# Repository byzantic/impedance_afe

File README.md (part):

# Impedance / C-V / DLTS / Electrochemistry Analog Front End: Rev B

**Status:** the Rev B **schematic** is done; the **PCB** is placed, the critical nets are hand-routed and locked, and the rest is autorouted (Freerouting): DRC 0 unconnected, 0 copper violations, parity 0; silkscreen not yet tidied. Rev A (schematic plus routed board, converted to KiCad 9/10) is kept in [`revA/`](revA/).

Fabrication outputs go in [GitHub Releases](../../releases), not in the repo. The parts list with debug and precision columns is in [`docs/BOM_revB.csv`](docs/BOM_revB.csv).

## Changes from Rev A
| Area | Rev A | Rev B |
|---|---|---|
| Drive input | single VIN BNC | **BIAS/PULSE** (DC) + **AC PROBE** (AC-coupled, ×1/×0.1 jumper) + **on-board 16-bit bias DAC**, summed (U9/U10) |
| C/G null | none | **vector nuller**: RV1 → fixed C (100 pF / 1 nF) and RV2 → fixed R (20 k / 2 k, AC-coupled), driven from the measured RE voltage |
| Calibration | none | T-switched on-board **10 k 0.1 %** and **100 pF 1 %** loads (CE_INT → WE) |
| Cell | always connected | **CELL relay** (K10) disconnects CE |
| High-gain ranges | 10k…100M | **1k**, 10k, 100k, 1M, 10M, 100M |
| V monitor | V_RE/2 only | V_OUT BNC switched by **VMODE**: DC (V_RE/2) or **AC ×10.1** (100 Hz HPF) |
| Control | 8 GPIOs → 74HCT541 | **Pico 2 or ESP32-S3-ETH** (socketed), SPI → 2× 74HC595 → 16 lines → 2× TBD62783A source drivers |
| Digitiser | scope only | adds an on-board **ADS131M04** (4-ch simultaneous, 24-bit) for standalone potentiostat work |
| Parts | SMD | **through-hole** throughout, except DAC/ADC (JLC-placed) and the SOIC half of the op-amp footprints |
| Op-amp footprint | SOIC-8 | **DIP-8 + SOIC-8 combo** (`afe:DIP-8_SOIC-8_Combo`): fit one package |
| Steering diodes | BAV199 (SOT-23) | 2N3904 collector-base junctions (TO-92) |

## Specifications (design values, not measured)
| Parameter | Value |
|---|---|
| Supplies | external ±15 V (screw terminal). On board: +5 V (L7805) and +3.3 V (MCP1700). Estimated ≲300 mA from +15 V (relays + Pico 2; an ESP32-S3-ETH adds roughly 150–350 mA on +5 V), ≲120 mA from −15 V |
| DUT drive | ±10 V, ≥ ±20 mA (op-amp limited), 47 Ω series to CE |
| BIAS/PULSE input | DC-coupled, Z_in ≈ 9.1 kΩ (10 k to virtual ground ∥ 100 k). JP1 = 50 Ω termination |
| AC PROBE input | AC-coupled. ×1: Z_in ≈ 9.1 kΩ, corner 16 Hz. ×0.1: Z_in ≈ 50 kΩ, corner 1.6 Hz. JP2 = 50 Ω termination, JP3 = gain |
| Bias DAC | DAC80502 channel A, 16-bit, +10.05 V … −10.05 V (≈0.31 mV/LSB), 0 V at midscale power-up; K21 connects it |
| High-gain TIA (±5 V out) | 1k: ±5 mA · 10k: ±500 µA · 100k: ±50 µA · 1M: ±5 µA · 10M: ±500 nA · 100M: ±50 nA |
| TIA feedback pole (precision Cf) | 1k: 7.2 MHz · 10k: 1.6 MHz · 100k: 720 kHz · 1M: 160 kHz · 10M/100M: set by strays (tens of kHz or less) |
| 1 MHz C-V ranges | **1k and 10k only**; calibrate gain and phase per range with the cal loads |
| Low-gain TIA | 499 Ω ∥ 68 pF, ±10 mA FS, takes over via the steering diodes when the high-gain TIA saturates (WE then sits ≈0.6 V off ground) |
| Null range | C: 0–100 pF, or 0–1.01 nF (NULL_RNG). G: ±50 µS, or ±505 µS (NULL_RNG) |
| Outputs (BNC, 50 Ω back-terminated) | V_OUT (DC: V_RE/2 · AC: ×10.1 V_RE), I_HI, I_LO |
| Other BNCs | CE, RE (shell = driven guard), GUARD, WE, BIAS/PULSE, AC PROBE, SYNC_IN (to controller pin 22, clamped) |
| ADC / DAC | On the **ADC/DAC HAT** (`adc_hat/`, Pi Zero pHAT outline) plugged onto J16/J17. ADS131M04, ±1.2 V FS behind the main board's /5.02 dividers (±6 V at the outputs). CH0 V_DC, CH1 I_HI, CH2 I_LO, CH3 V_AC. Clock: Pico GP21 GPOUT0 at 8.000 MHz (USB PLL / 6; data rates ×0.977) via J16-7 by default, or the HAT's 8.192 MHz oscillator (HAT JP1). DAC80502 dual DAC also on the HAT (A = bias, B spare on J2 pin 9) |

## Blocks (schematic sheet regions)
| Block | Refs | Notes |
|---|---|---|
| Power | J1, D1–D3, FB1–FB5, U25, U26 | Controller VSYS fed via D3. Controller ground via FB5 (JP5 hard-ties it) |
| Inputs / summer | J2, J3, U9, U10, K21 | VSET = V_bias + V_dac + k·V_ac (two inverting stages). J2/J3 are on the back edge |
| Bias DAC | HAT U2, U11 | level shift on the main board: V = 10.05 V − 4.02·V_DAC. DAC_OUT/DAC_REF arrive on J17. SPI2C strap is on the HAT (R2 = SPI, JP2 = I2C); R6 pulls RSTSEL high (midscale at power-up) |
| Control amp | U1, K7 (DEV), K8 (PSTAT) | DEV: follower. PSTAT: PI (C15 100 p, R15 1 k, R16 10 k): retune for your cells |
| Cell / cal | K9 (RE_LOCAL), K10 (CELL), K11–K14, R18, C16 | cal mid-nodes are grounded by NC relays when off, so the open contacts see 0 V across them (no leakage into WE) |
| RE / guard / monitors | U2, U3, U7, U4, U8, K19/K20 | U7 (RE_MON) feeds the monitors and the nuller, keeping their load off the electrometer U2 |
| Nuller | U12–U14, RV1, RV2, J14, J15, K15–K18 | inject at SUM_HI. C path: −jωC·V. G path: AC-coupled, bipolar. RV1/RV2 are front-panel 10-turn pots on J14/J15 (Molex KK 254: 1 CW, 2 wiper, 3 CCW, 4 cable shield) |
| TIAs | U5 (K1–K6, R41–R46, C41–C46), Q1/Q2, U6 | relays on the output side of the feedback networks |
| ADC link | J16 (Pi 40-pin, male), J17 (1×12 analog, male), R47, R50–R57, C50–C53 | dividers + 10 nF (≈20 kHz) on the main board, one row per channel level with its J17 pin. J17: 1 ADC0P, 3 ADC1P, 5 ADC2P, 7 ADC3P, 10 DAC_OUT, 11 DAC_REF; 2/4/6/8/12 GND (ADCn N tied to GND here); 9 unconnected (HAT DAC_OUTB) |
| Controller | A1 (Pico 2 or ESP32-S3-ETH), U27/U28 (74HC595), U22/U23, R76, J13 | 4.7 k pulls set the power-up state; RLY_OE (R76 pull-up) holds the 595 outputs off until firmware enables them |

## Control map
The 16 relay lines CTL*n* come from two 74HC595s on SPI0 (MOSI → U27 → U28; SCK shared with the HAT, latch = RLY_LATCH). Shift 16 bits, pulse RLY_LATCH, then drive RLY_OE low. RLY_OE is pulled high (R76), so the 595 outputs stay Hi-Z through power-up and reset and the 4.7 k pulls set the state. **CTL*n* drives driver channel 15−*n*** (KD(15−*n*)); the order is for routing, and firmware maps it. Exactly one range at a time; use break-before-make, ~2 ms per reed operation.

| CTL | 595 output | Driver ch (KD) | Function | Relays | Power-up |
|---|---|---|---|---|---|
| 0 | U27 QA | 15 | DAC_EN | K21 | off |
| 1 | U27 QB | 14 | VMODE_AC | K19 (NC) + K20 | off (= DC) |
| 2 | U27 QC | 13 | NULL_RNG (1 nF / 2 k) | K17 + K18 | off |
| 3 | U27 QD | 12 | NULL_EN | K15 + K16 | off |
| 4 | U27 QE | 11 | CAL_C | K13 + K14 | off |
| 5 | U27 QF | 10 | CAL_R | K11 + K12 | off |
| 6 | U27 QG | 9 | CELL (CE_INT ↔ CE BNC) | K10 | off |
| 7 | U27 QH | 8 | RE_LOCAL (RE ↔ CE_INT) | K9 | **on** |
| 8 | U28 QA | 7 | PSTAT (PI loop) | K8 | off |
| 9 | U28 QB | 6 | DEV (U1 follower) | K7 | **on** |
| 10 | U28 QC | 5 | range 100M | K6 | off |
| 11 | U28 QD | 4 | range 10M | K5 | off |
| 12 | U28 QE | 3 | range 1M | K4 | **on** |
| 13 | U28 QF | 2 | range 100k | K3 | off |
| 14 | U28 QG | 1 | range 10k | K2 | off |
| 15 | U28 QH | 0 | range 1k | K1 | off |

**Controller header (A1).** The pins are chosen so that a Pico 2 and a Waveshare ESP32-S3-ETH (same header, 72.8 mm long, RJ45/USB-C at the USB end) both work. ESP32 pins avoided: 1–2 (USB), 6–7 (straps), 15–17 and 19–20 (octal PSRAM), 35 (RGB LED).

| Pin | Pico 2 | ESP32-S3-ETH | Net |
|---|---|---|---|
| 4 | GP2 | IO48 | RLY_LATCH |
| 5 | GP3 | IO47 | RLY_OE |
| 21 | GP16 | IO43 (UART0 TX: boot log) | AUX (J13-10) |
| 22 | GP17 | IO44 | SYNC_IN |
| 24 | GP18 | IO0 (boot strap; HAT R5 pulls it high) | ADC_SYNC |
| 25 | GP19 (SPI0 TX) | IO1 | MOSI |
| 26 | GP20 (SPI0 RX) | IO2 | MISO |
| 27 | GP21 (GPOUT0, 8.000 MHz) | IO3 (leave as input) | PICO_GPCLK → R47 → HAT_CLK |
| 29 | GP22 (SPI0 SCK) | IO15 | SCK |
| 31 | GP26 | IO18 | CS_ADC |
| 32 | GP27 | IO16 | CS_DAC |
| 34 | GP28 | IO17 | ADC_DRDY |

Free on both: pins 9–12 (GP6–GP9 / IO42–IO39). With an ESP32-S3 the HAT runs from its own 8.192 MHz oscillator (fit Y1, HAT JP1 2-3).

J16 uses the Raspberry Pi pinout, so the HAT also stacks on a Pi Zero: SPI0 on 19/21/23, CE0 (24) = CS_ADC, CE1 (26) = CS_DAC, GPIO4 (7, GPCLK0) = clock, GPIO24 (18) = SYNC/RESET, GPIO25 (22) = DRDY, 3V3 on 1/17 (HAT logic), 5V on 2/4 (HAT AVDD LDO and DAC).

J13 (2×8 right-angle box header, back-right corner) carries SPI, CS_ADC, CS_DAC, DRDY, ADC_SYNC, SYNC_IN, HAT_CLK (9), AUX (10), RLY_LATCH (11), RLY_OE (12), RUN (13) and GND (14–16): an external 3.3 V SPI master can run the relays and the HAT with the controller absent or held in reset (RUN low), using the HAT oscillator (HAT JP1 2-3) or its own clock on J13-9.

**Mode recipes**
- **Device mode (C-V, DLTS):** DEV=1, PSTAT=0, RE_LOCAL=1 (or 0 with a separate RE lead to the DUT), CELL=1.
- **Potentiostat:** DEV=0, PSTAT=1, RE_LOCAL=0, CELL=1. Switch CELL on last and off first.
- **Calibrate:** CELL=0, RE_LOCAL=1, DEV=1, then CAL_R=1 (or CAL_C=1). Record I/V gain and phase for each range at the probe frequency.
- **Null (C-DLTS):** DUT connected at the bias point, NULL_RNG as needed, NULL_EN=1. Adjust RV1 for minimum 1 MHz on I_HI, then RV2, then iterate.

## Build variants
Each BOM line has a **debug** and a **precision** column.

| Position | Debug | Precision |
|---|---|---|
| U1, U2, U3, U5, U6, U7, U8, U13 (1 MHz or sensitive path) | OPA134PA | OPA828ID (SOIC half) or OPA627AP (DIP) |
| U4, U9, U10, U11, U12, U14 | OPA134PA | OPA134PA |
| TIA Cf (1k/10k/100k/1M) | 47p / 15p / 4.7p / 1.5p | 22p / 10p / 2.2p / 1p |
| Rf | 1 % metal film | 1k–100k metal foil; 1M–100M glass high-megohm |
| K5, K6 (10M, 100M) | generic SIP-1A05 | Coto 9007-class ≥10¹² Ω (**footprint differs: check**) |
| RV1, RV2 | 10-turn panel pots with counting dials (Bourns 3590S-2-103), off-board via J14/J15 | same |

The NE5534 can't be used: it needs compensation pins, which this footprint doesn't wire.

**Rough cost per board** (from memory, not quoted): debug ≈ $110–190; precision adds ≈ $150–260 (8× OPA828 is about $65–95 of that). A batch of bare PCBs is about $40–80, plus the ADC/DAC HAT (all SMD, JLC-assembled; ADS131M04 + DAC80502 are most of its cost).

## Layout (Rev B: placed, pre-routed, autorouted)
- **Front edge (bottom):** CE, RE (shell = GUARD), GUARD, WE, I_LO, I_HI, V_OUT. I_LO and I_HI are swapped relative to the schematic order so that their lanes, and V_OUT's, run down to the BNCs to the right of the SUM_HI bus end, with no crossings of SUM_HI.
- **Board:** 248 × 150 mm. Front BNC pitch 26.5 mm either side of RE (insulated GUARD-shell socket), 24 mm on the output group. GUARD (J6) stays left of K11, the left end of the SUM_HI bus, so the guard run never crosses the bus.
- **Back edge (top):** J1 power, AC PROBE and BIAS/PULSE (24 mm pitch), the 74HC595s, controller (RJ45/USB end), SYNC_IN (~23 mm clear of the controller), J13 (back-right corner). Nuller pots on cables (J14/J15) to the front panel.
- **Controller (A1):** footprint `afe:Pico2_ESP32-S3-ETH_THT`. The ESP32-S3-ETH's RJ45/USB-C end reaches the back edge; a Pico 2's USB socket then sits ~18 mm in from the edge. The ESP32's microSD slot is underneath at the far end and the card goes in from that end: keep the 15 mm area below the module (User.Comments) free of tall parts.
- **Relay control:** 595 (outputs on its lower row) → pull resistor → driver input, one column per line, 3 mm in from the back edge so tracks can pass above the 595s. The area under the drivers is left clear for the 16 coil lines.
- **Op-amp decoupling** book-ends each socket: C+ at the pin-7 end, C− at the pin-4 end. U2, U5 and U6 (RE input and the two TIAs) keep hand-placed caps.
- **Nuller:** U12 sits between the null buffers U13/U14, with J14/J15 either side of it. A Bourns 3296W multi-turn trimmer fits J14/J15 pads 1–3 (in-line, 2.54 mm, wiper in the middle) for a permanent fixture; check the CW sense against the panel-pot wiring.
- **TIA ladder:** about 10–11 mm column pitch, ≥1.4 mm between parts, and a ~4 mm clear area between U5 −IN and R46 for an optional PTFE standoff. The SUM_HI guard is a GND pour with stitching vias and a mask-free band (a closed ring can't fit inside the combo footprint).
- **HAT:** below J13 at the back-right, rotated 90°, on 11 mm M2.5 standoffs (H10–H13). Keep parts under it short. The ADC dividers sit in one row per channel left of J17, level with the ADCnP pins. HAT connectors: J1 Pi 40-pin socket (bottom); J2 1×12 analog row along the bottom edge (IN0P, IN0N … IN3P, IN3N, DAC_OUTB, DAC_OUT, DAC_REF, GND): a socket on the bottom for the AFE, or 2.54 mm screw terminals on top for general use; J3 2×6 MCU/cable header on the right-hand short edge (1 +5V, 2 GND, 3 +3V3, 4 GND, 5 SCLK, 6 MOSI, 7 MISO, 8 CS_ADC, 9 CS_DAC, 10 DRDY, 11 SYNC, 12 CLK_IN; the host supplies 5 V and 3.3 V). Y1 takes a DIP-8 half-size can (hand-solder) or a 3.2 × 2.5 mm SMD part on pads inside it (`afe:Oscillator_DIP-8_ASE-3.2x2.5_Combo`). The HAT is routed (`scripts/hat/route.py`): SMD on top with GND fan-out vias to the bottom plane, a no-track strip above the Pi header's edge row so its GND pins keep their pour, U2 (DAC80502, WSON-10) has locked escapes on its left-hand pins and ADC_CLK is a locked 0.3 mm run from JP1 to U1 (Clock net class); everything else autorouted.
- **Mounting holes:** H1 (by J1, the star point) is the only chassis bond. H2–H9 are isolated M3 NPTH holes: front edge ×5 (H2, H7, H3, H4, H5), back edge ×1, centre ×2.
- Combo footprints: same-numbered DIP and SOIC pads are joined with copper on every op-amp (followers also get the pin 2–6 link inside the package). The SOIC pads for pins 1, 5 and 8 are unnumbered (mechanical only): those pins are NC on every op-amp used here, so a part that uses them (offset trim, duals) would need the footprint changed.
- Autorouting: GND is left to the pours (its pins are taken out of the router's netlist); everything else, including PICO_GND, is routed, with bottom-layer track cost ×3 to keep the bottom plane whole. The null-pot wipers (J14/J15 → U13/U14 +IN) and the op-amp decoupling links are pre-routed.
- The L7805 dissipates about 1.5 W: fit a heatsink (keep-clear area on User.Comments).

## Verification status
- Main schematic: netlist checked against `scripts/design.py` (**208 nets, 0 problems**); KiCad 9 ERC 0 errors (16 `lib_symbol_mismatch` warnings from the local KiCad 9 libraries).
- HAT schematic: checked against `scripts/hat/design.py` (**59 nets, 0 problems**); ERC 0 errors.
- HAT/main connectors: pad positions match under the mounting transform (0.000 mm), pin nets match.
- Not simulated. Compensation values are hand calculations.

## Open items / things to verify before layout
1. **DAC output range.** SPI2C is settled: low = SPI (DAC80502 datasheet SBAS793A), the R2 default. The level shift assumes the 0–5 V output range (VDD = 5 V). The top few codes may clip, so firmware should limit them. K21 stays open until the DAC is configured.
2. **Reed relay pinout** (Standex/Meder SIL, 1A and 1B): contact on 1–7, coil on 3–5.
3. **2N3904 C-B leakage** isn't a datasheet guarantee. Measure it, or fit an SMD BAV199 on an adapter.
4. **Controller supply with an ESP32-S3-ETH:** it draws roughly 150–350 mA from +5 V (W5500 plus Wi-Fi peaks), which adds 1.5–3.5 W to the L7805 (from +15 V). Check the heatsink, or feed the module from its own USB-C/PoE. The ESP32 header map is from Waveshare's dimension drawing (underside silk); confirm on a real module.
5. TBD62783A has internal output clamp diodes and VIN(on) of 2.0 V minimum; the 74HC595 runs from +3V3D.
6. **PI loop** (C15/R15/R16) and the AC monitor/TIA phase matching need tuning and calibration on real hardware.
7. **ADS131M04 at 8.000 MHz:** confirm the CLKIN range in the datasheet. HAT oscillator Y1 part number is TBD (DIP-8 half-size can or 3.2 × 2.5 mm SMD, 3.3 V CMOS, 8.192 MHz).
8. Firmware is not written yet (MicroPython suggested: relay sequencing, DAC/ADC drivers, calibration).

## Regenerating / checking
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
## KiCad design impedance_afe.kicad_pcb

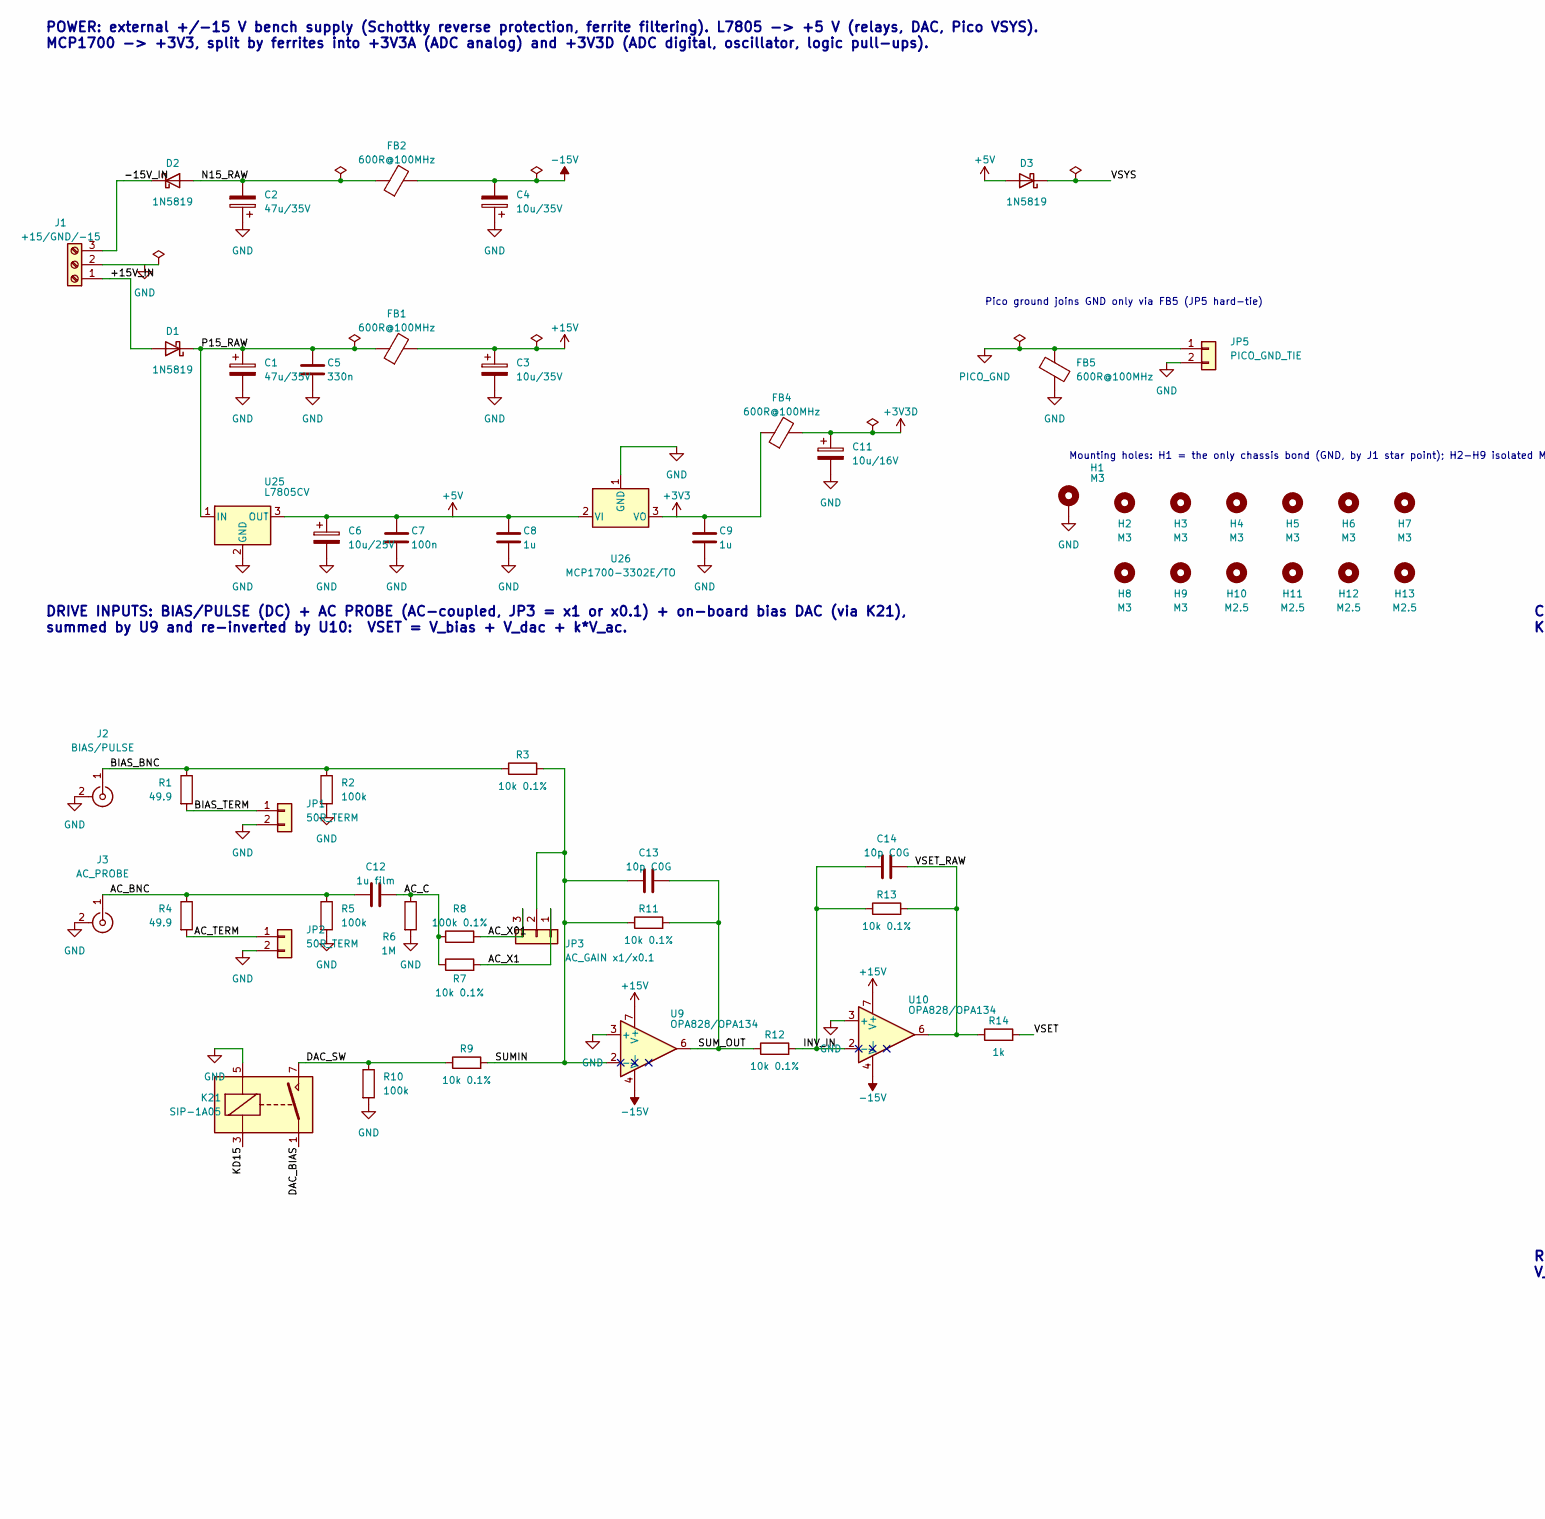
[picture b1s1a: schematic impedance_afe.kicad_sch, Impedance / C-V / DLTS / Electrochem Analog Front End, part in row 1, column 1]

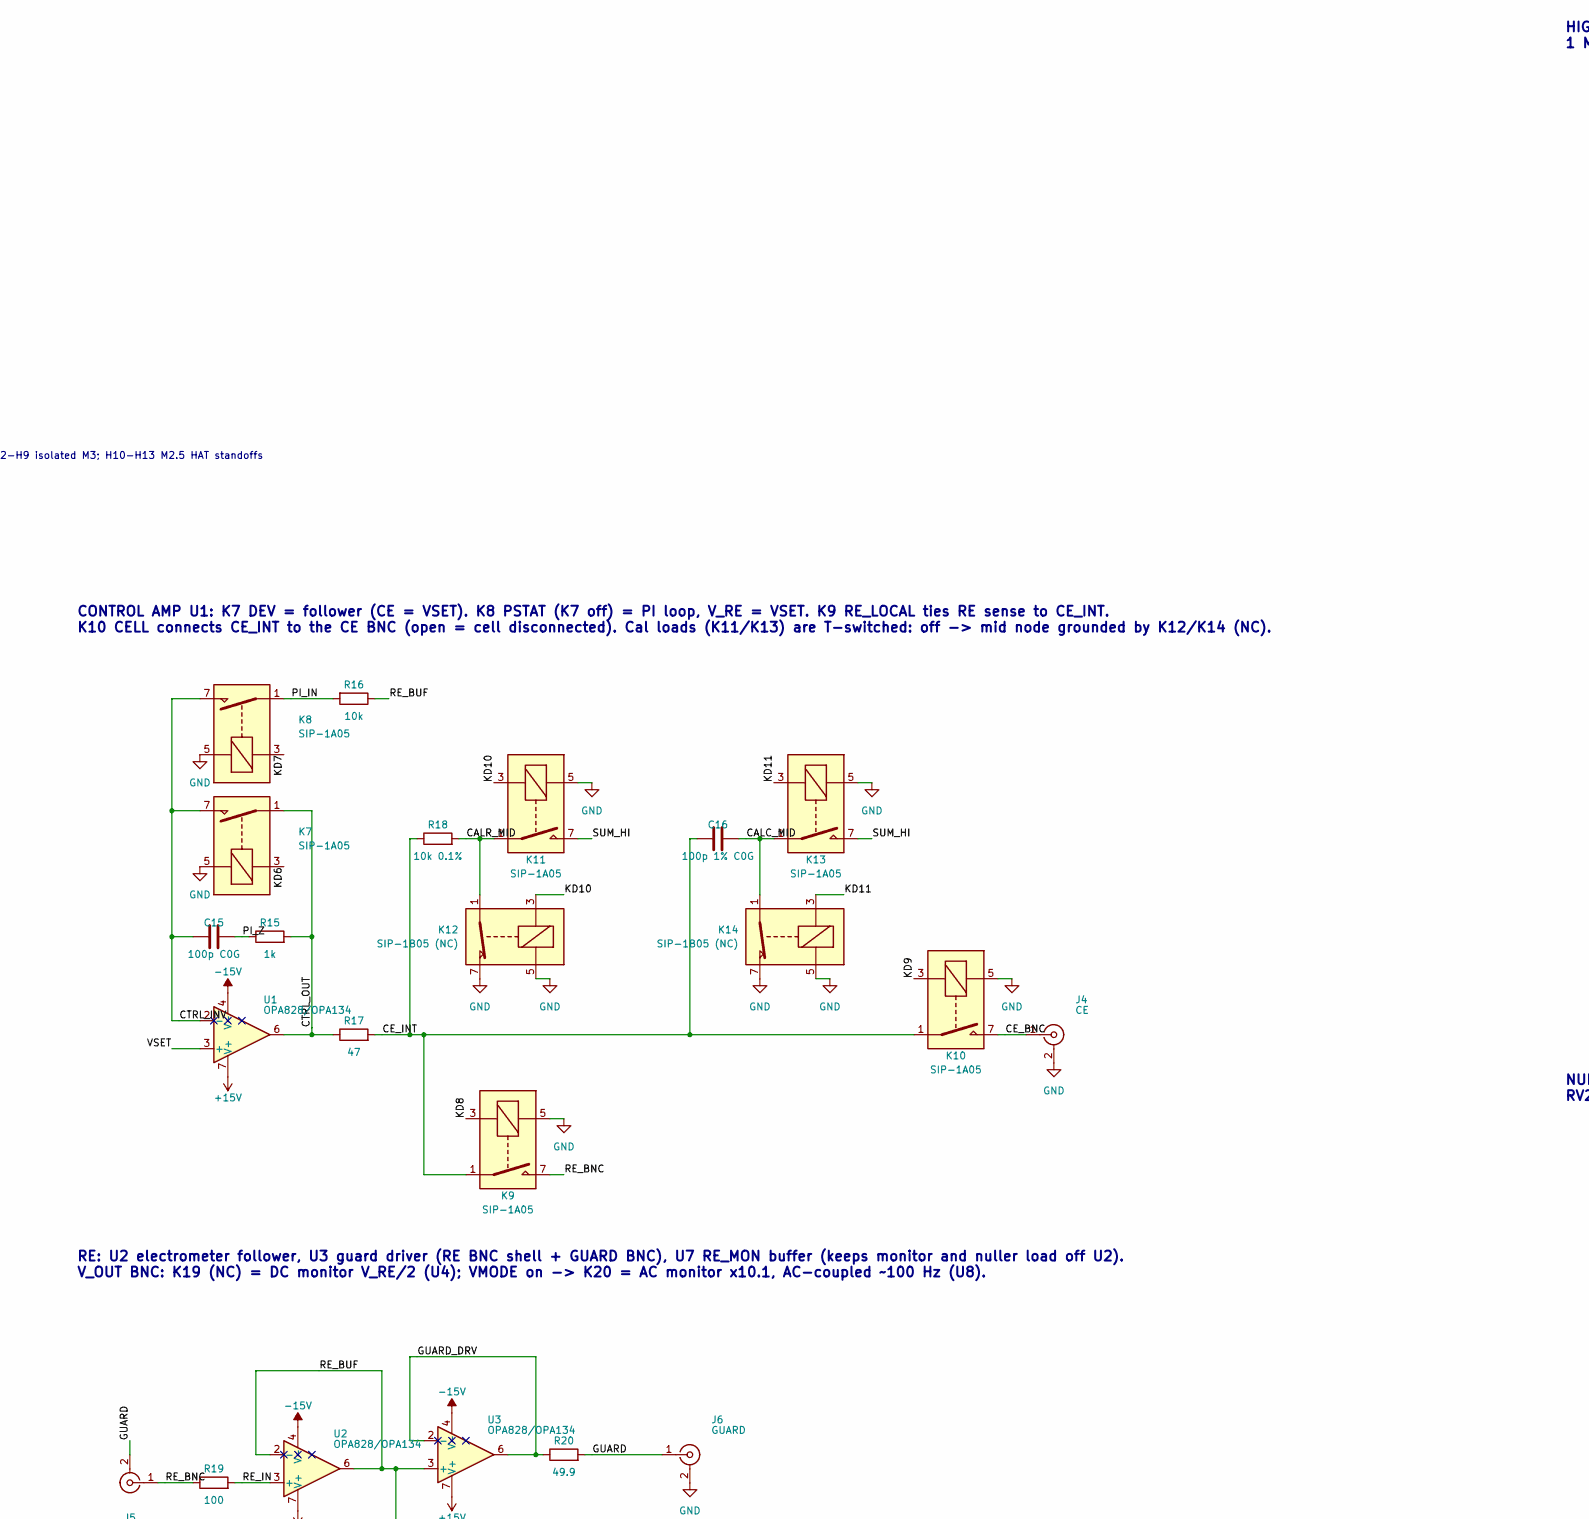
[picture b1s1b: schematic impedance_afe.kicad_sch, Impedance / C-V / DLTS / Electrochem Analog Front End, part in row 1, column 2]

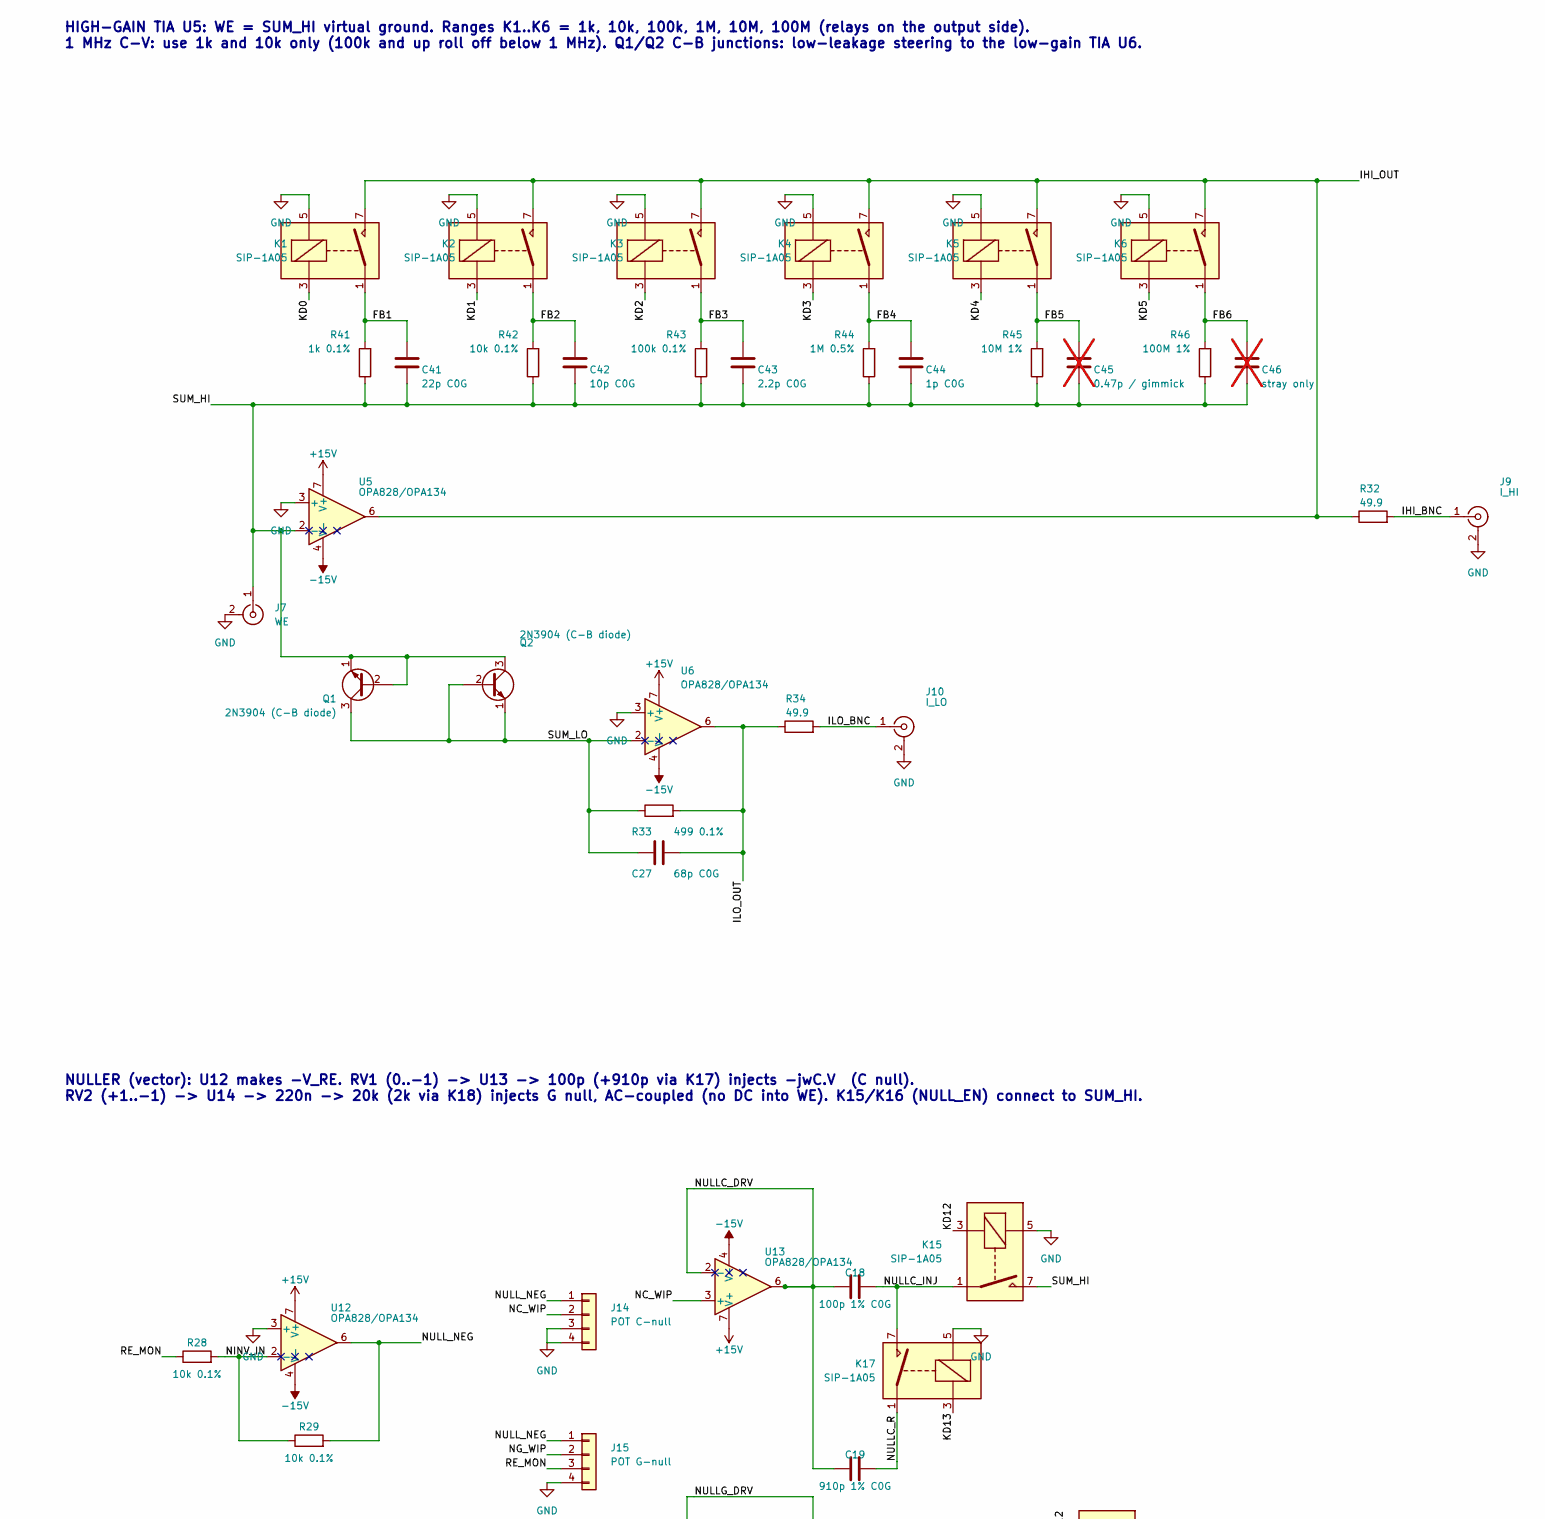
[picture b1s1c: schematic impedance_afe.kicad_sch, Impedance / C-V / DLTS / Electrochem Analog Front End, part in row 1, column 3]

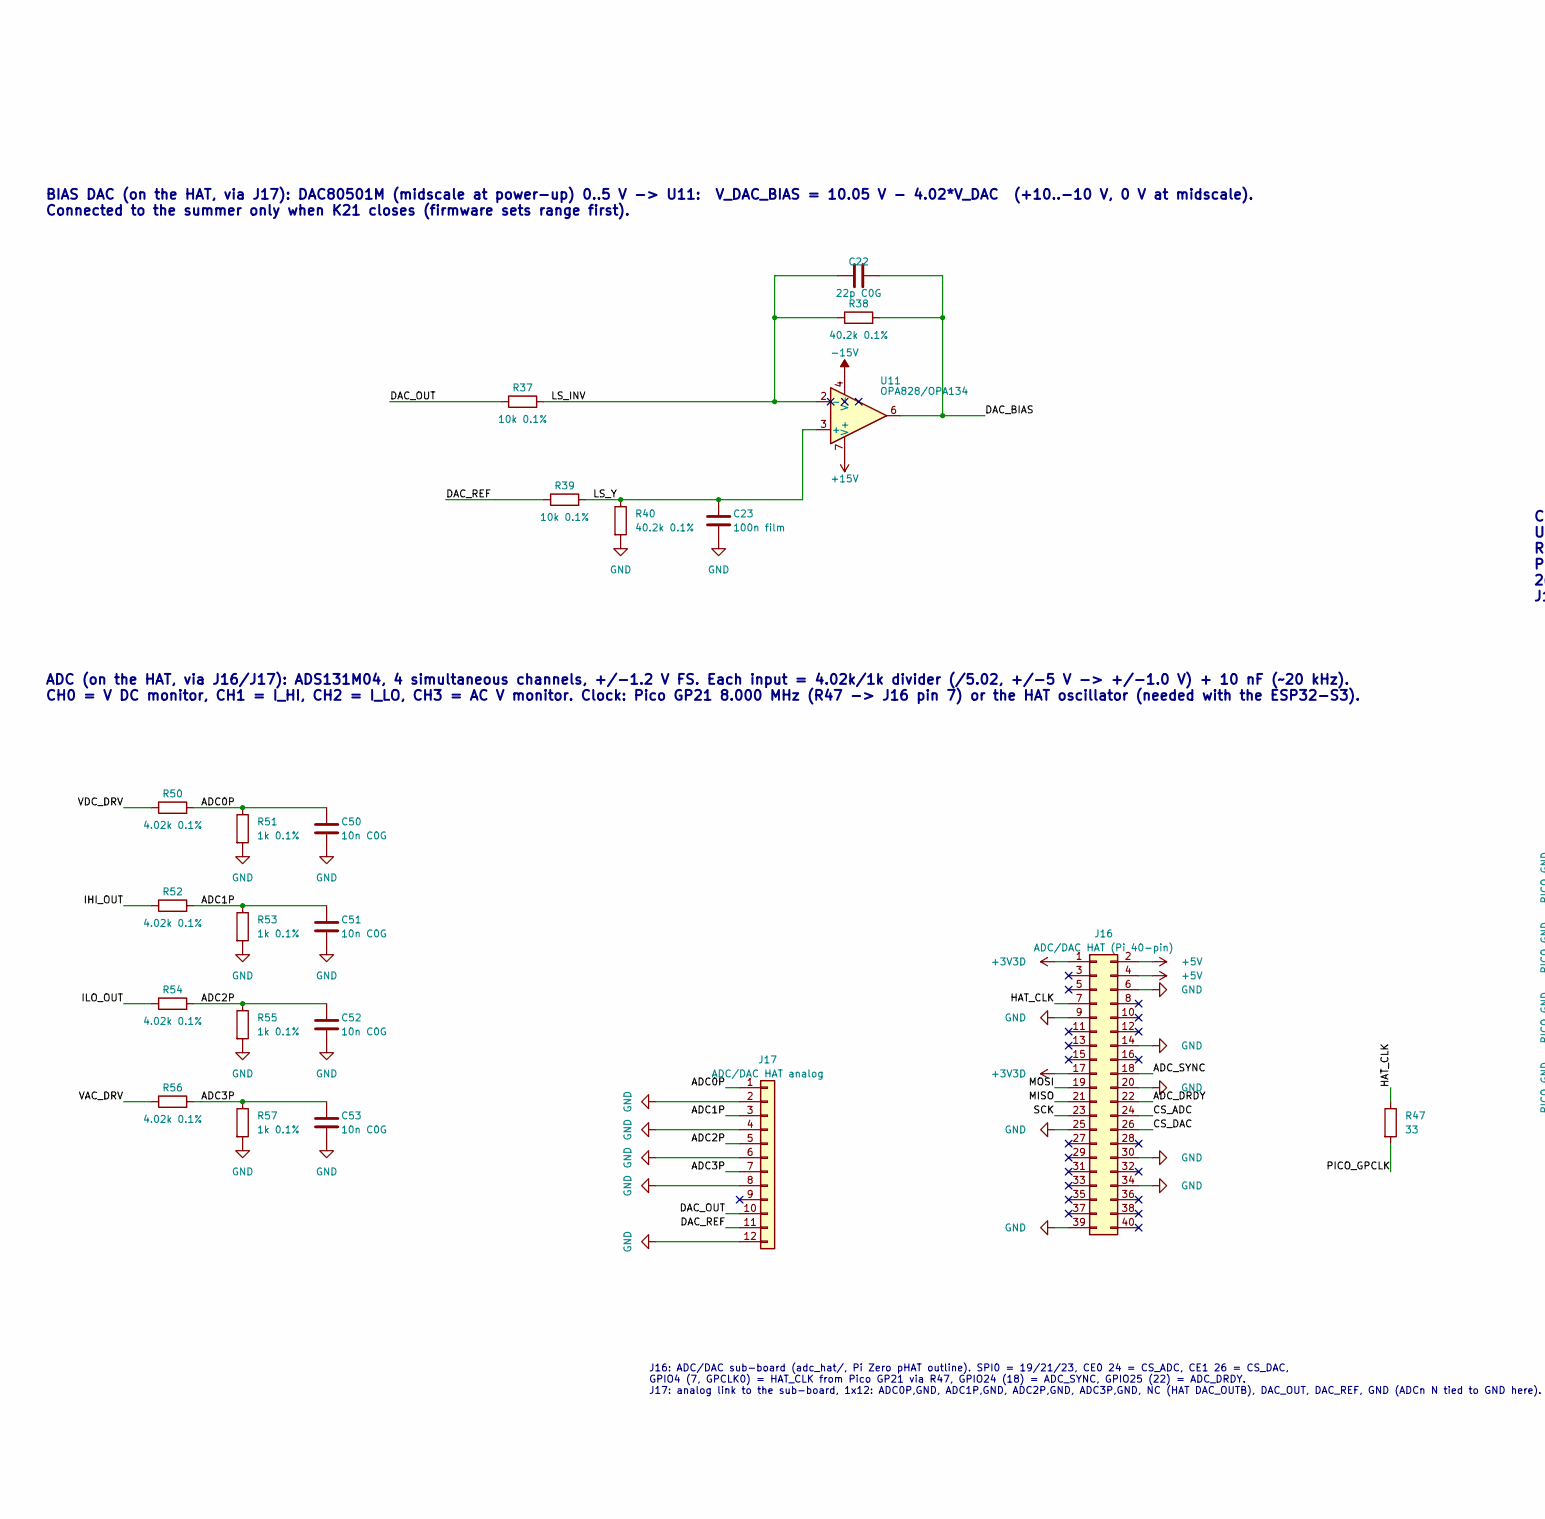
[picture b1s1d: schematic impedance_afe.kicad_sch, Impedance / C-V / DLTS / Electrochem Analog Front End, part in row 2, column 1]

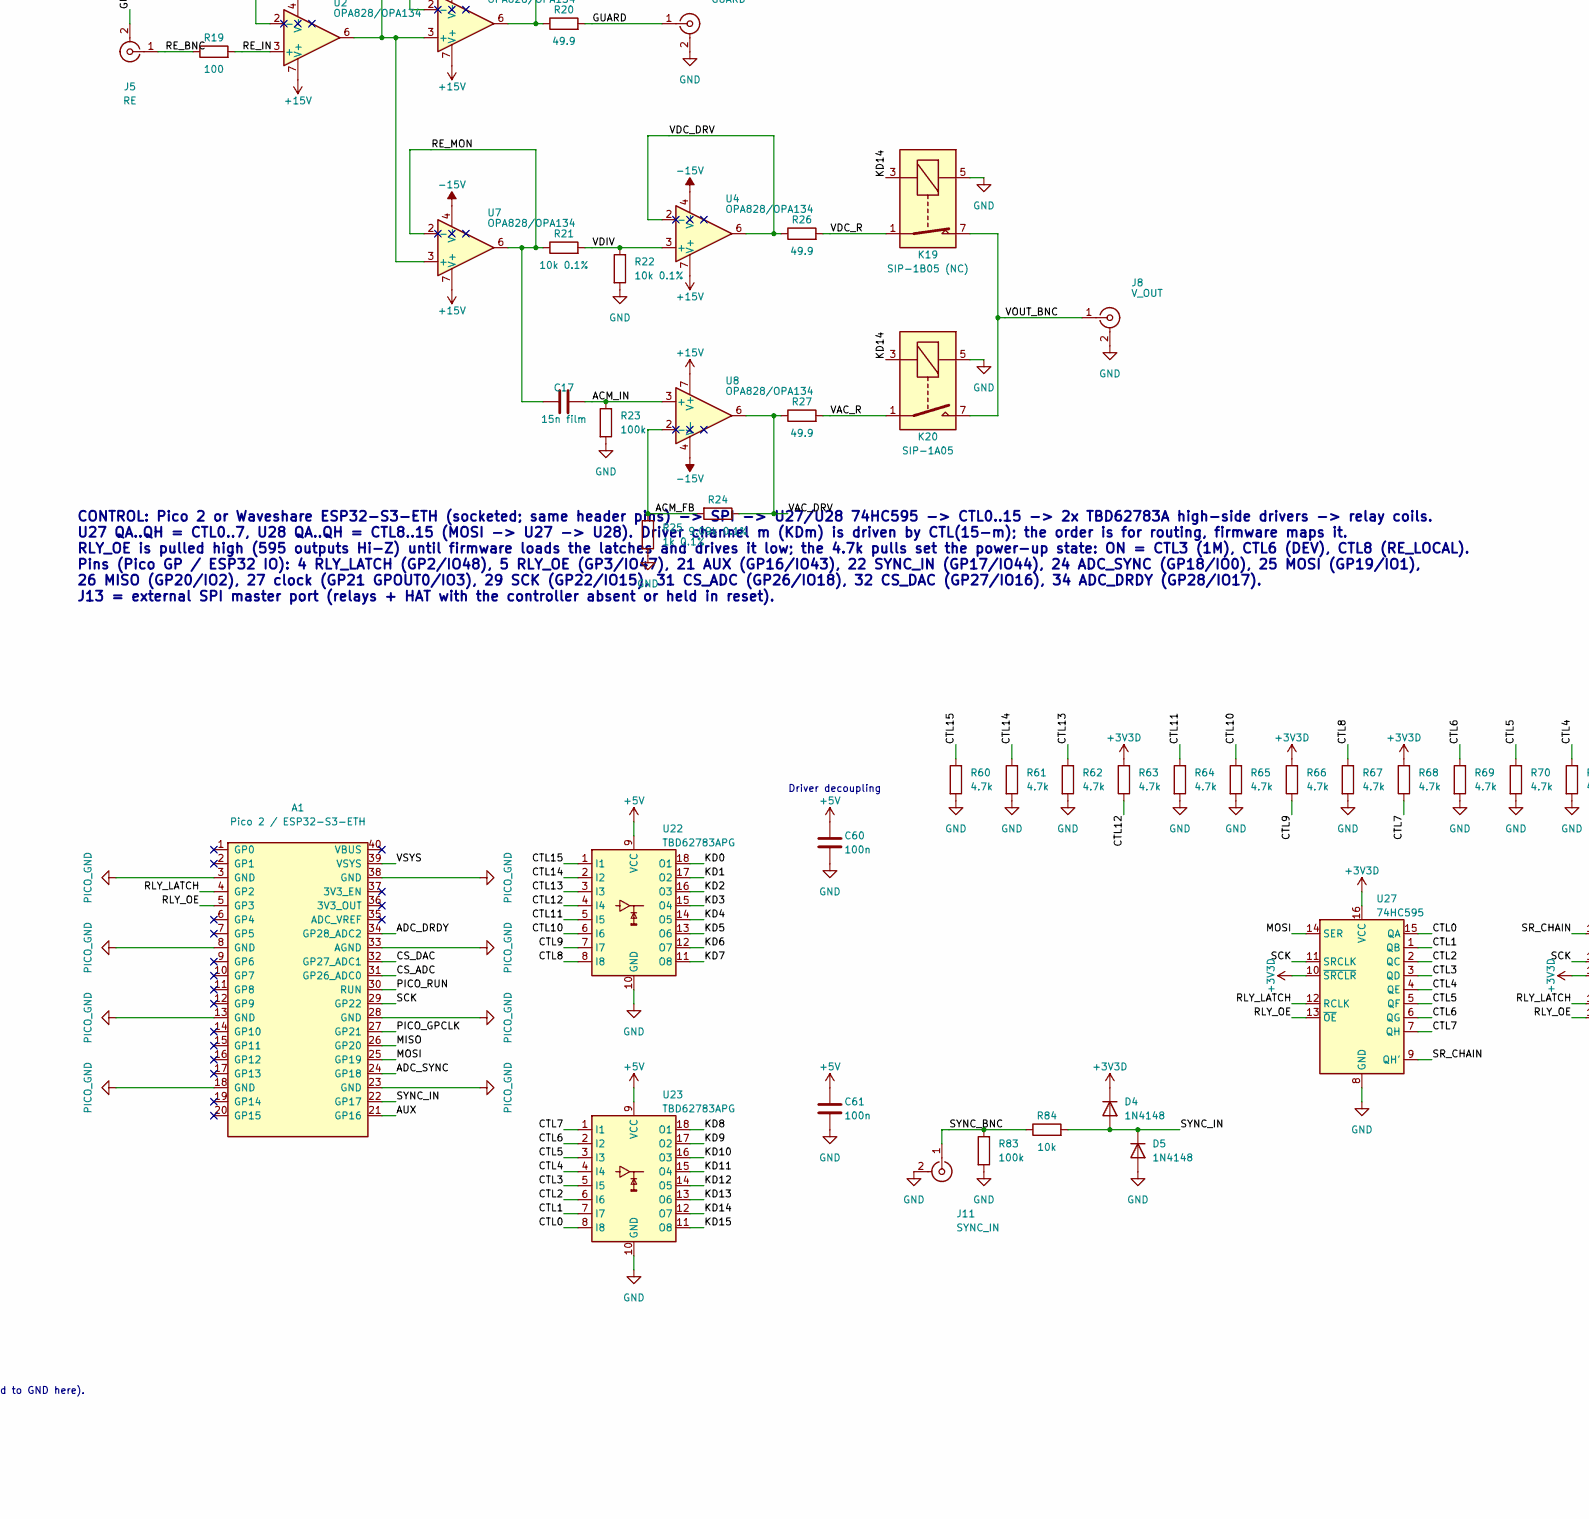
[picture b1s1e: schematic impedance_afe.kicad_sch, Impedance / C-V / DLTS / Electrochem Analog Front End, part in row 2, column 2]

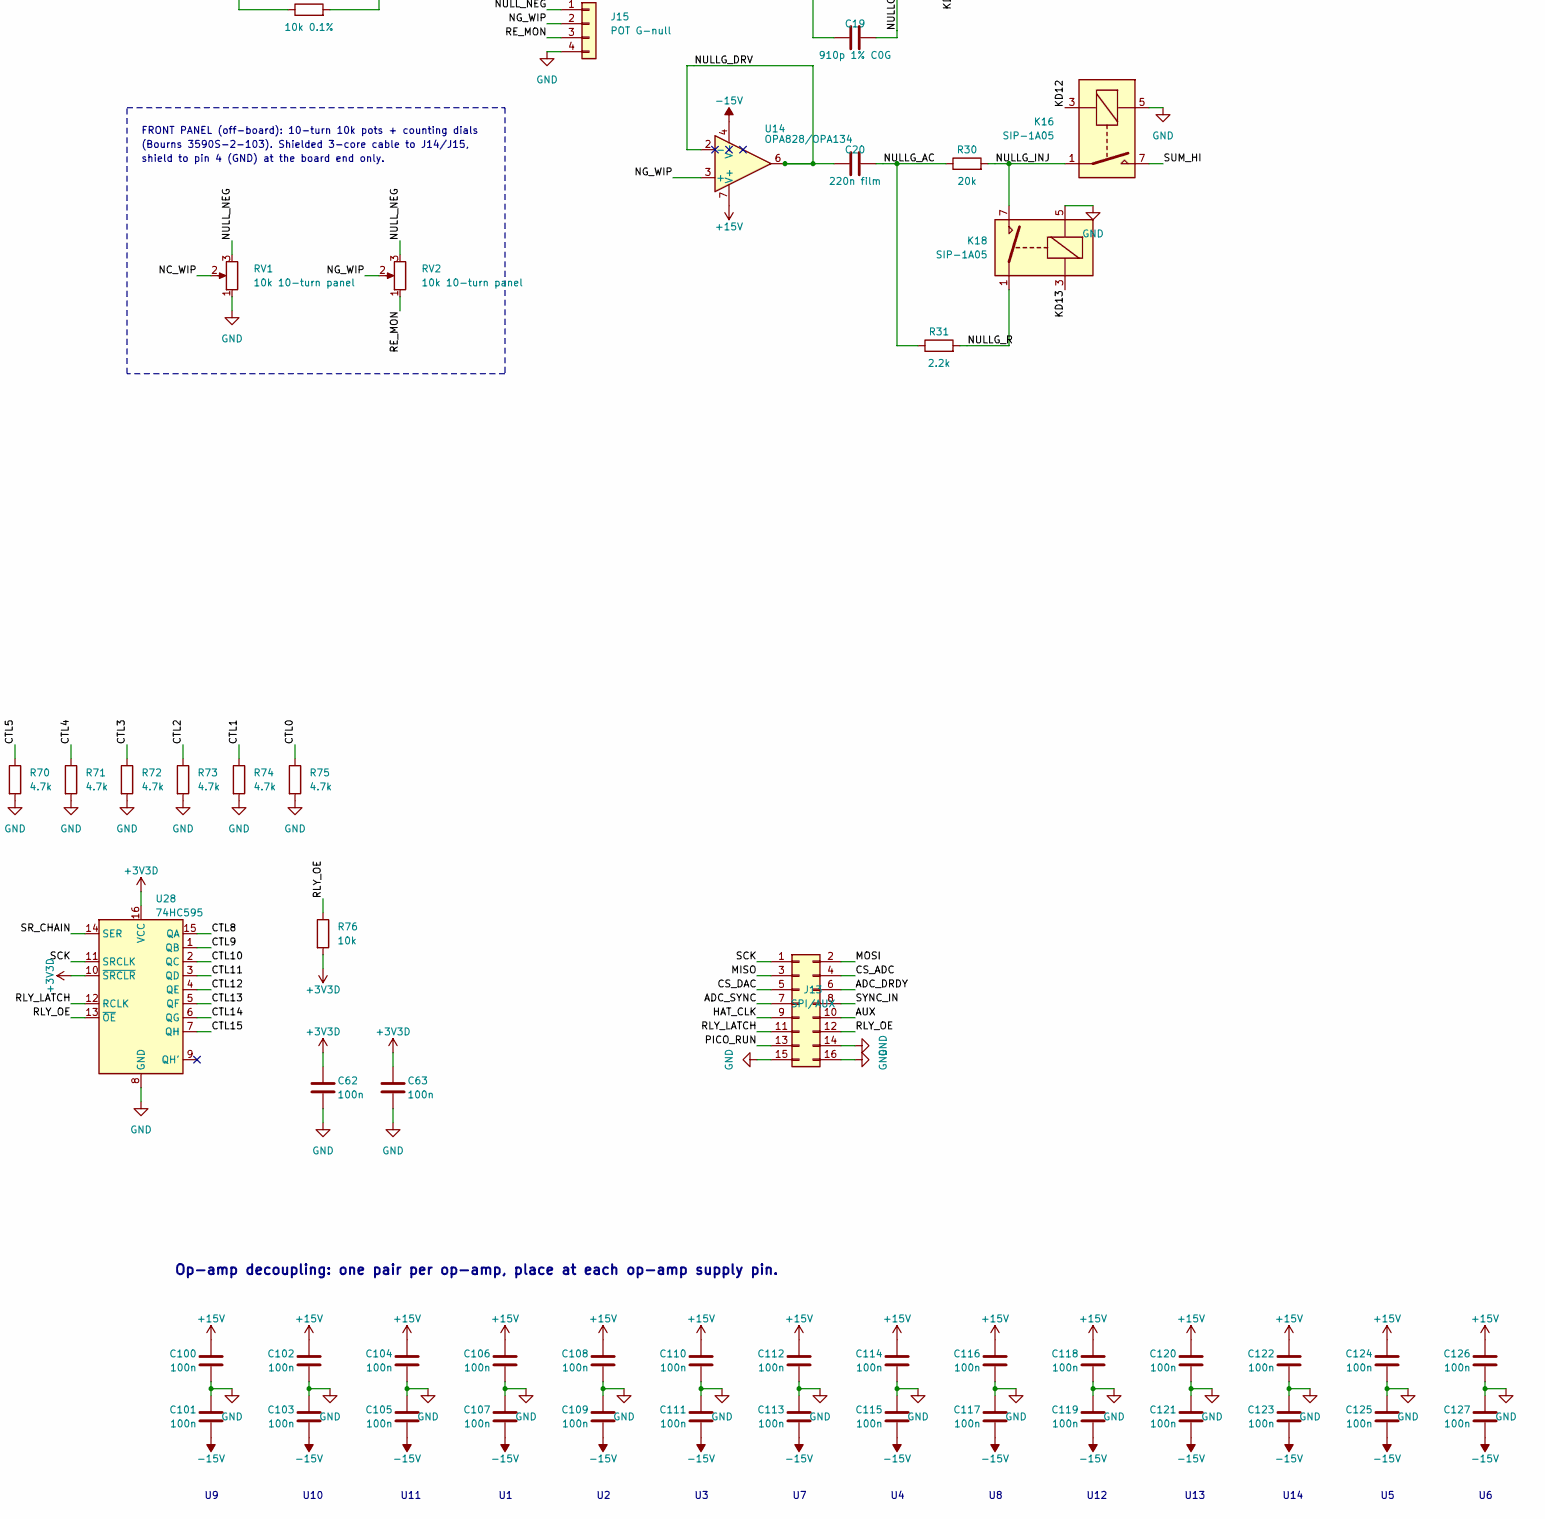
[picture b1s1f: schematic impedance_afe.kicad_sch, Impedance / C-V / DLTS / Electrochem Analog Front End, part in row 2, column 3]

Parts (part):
A1: Pico 2 / ESP32-S3-ETH; Pico2_ESP32-S3-ETH_THT; MPN SC1631 (Pico 2) or Waveshare ESP32-S3-E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
C1, C2: 47u/35V; CP_Radial_D6.3mm_P2.50mm
C3, C4: 10u/35V; CP_Radial_D6.3mm_P2.50mm
C5: 330n; C_Disc_D5.0mm_W2.5mm_P5.00mm
C6: 10u/25V; CP_Radial_D6.3mm_P2.50mm
C7, C60, C61, C100, C101, C102, C103, C104, C105, C106, C107, C108, C109, C110, C111, C112, C113, C114, C115, C116, C117, C118, C119, C120, C121, C122, C123, C124, C125, C126, C127: 100n; C_Disc_D5.0mm_W2.5mm_P5.00mm
C8, C9: 1u; C_Disc_D5.0mm_W2.5mm_P5.00mm
C11: 10u/16V; CP_Radial_D6.3mm_P2.50mm
C12: 1u film; C_Rect_L7.2mm_W2.5mm_P5.00mm_FKS2_FKP2_MKS2_MKP2
C13, C14, C42: 10p C0G; C_Disc_D3.0mm_W1.6mm_P2.50mm
C15: 100p C0G; C_Disc_D3.0mm_W1.6mm_P2.50mm
C16, C18: 100p 1% C0G; C_Disc_D3.0mm_W1.6mm_P2.50mm
C17: 15n film; C_Rect_L7.2mm_W2.5mm_P5.00mm_FKS2_FKP2_MKS2_MKP2
C19: 910p 1% C0G; C_Disc_D3.0mm_W1.6mm_P2.50mm
C20: 220n film; C_Rect_L7.2mm_W2.5mm_P5.00mm_FKS2_FKP2_MKS2_MKP2
C22, C41: 22p C0G; C_Disc_D3.0mm_W1.6mm_P2.50mm
C23: 100n film; C_Rect_L7.2mm_W2.5mm_P5.00mm_FKS2_FKP2_MKS2_MKP2
C27: 68p C0G; C_Disc_D3.0mm_W1.6mm_P2.50mm
C43: 2.2p C0G; C_Disc_D3.0mm_W1.6mm_P2.50mm
C44: 1p C0G; C_Disc_D3.0mm_W1.6mm_P2.50mm
C45: 0.47p / gimmick; C_Disc_D3.0mm_W1.6mm_P2.50mm; not fitted
C46: stray only; C_Disc_D3.0mm_W1.6mm_P2.50mm; not fitted
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
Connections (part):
+3V3: C9.1, FB4.1, U26.3 (VO)
+3V3D: C11.1, C62.1, C63.1, D4.1 (K), FB4.2, J16.1, J16.17, R63.2, R66.2, R68.2, R76.2, U27.10 (~SRCLR), U27.16 (VCC), U28.10 (~SRCLR), U28.16 (VCC)
+5V: C6.1, C7.1, C8.1, C60.1, C61.1, D3.2 (A), J16.2, J16.4, U22.9 (VCC), U23.9 (VCC), U25.3 (OUT), U26.2 (VI)
+15V: C3.1, C100.1, C102.1, C104.1, C106.1, C108.1, C110.1, C112.1, C114.1, C116.1, C118.1, C120.1, C122.1, C124.1, C126.1, FB1.2, U1.7 (V+), U2.7 (V+), U3.7 (V+), U4.7 (V+), U5.7 (V+), U6.7 (V+), U7.7 (V+), U8.7 (V+), U9.7 (V+), U10.7 (V+), U11.7 (V+), U12.7 (V+), U13.7 (V+), U14.7 (V+)
-15V: C4.2, C101.2, C103.2, C105.2, C107.2, C109.2, C111.2, C113.2, C115.2, C117.2, C119.2, C121.2, C123.2, C125.2, C127.2, FB2.2, U1.4 (V-), U2.4 (V-), U3.4 (V-), U4.4 (V-), U5.4 (V-), U6.4 (V-), U7.4 (V-), U8.4 (V-), U9.4 (V-), U10.4 (V-), U11.4 (V-), U12.4 (V-), U13.4 (V-), U14.4 (V-)
/+15V_IN: D1.2 (A), J1.1
/-15V_IN: D2.1 (K), J1.3
/ACM_FB: R24.2, R25.1, U8.2 (-)
/ACM_IN: C17.2, R23.1, U8.3 (+)
/AC_BNC: C12.1, J3.1 (In), R4.1, R5.1
/AC_C: C12.2, R6.1, R7.1, R8.1
/AC_TERM: JP2.1, R4.2
/AC_X01: JP3.3, R8.2
/AC_X1: JP3.1, R7.2
/ADC0P: C50.1, J17.1, R50.2, R51.1
/ADC1P: C51.1, J17.3, R52.2, R53.1
/ADC2P: C52.1, J17.5, R54.2, R55.1
/ADC3P: C53.1, J17.7, R56.2, R57.1
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
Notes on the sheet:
ADC (on the HAT, via J16/J17): ADS131M04, 4 simultaneous channels, +/-1.2 V FS. Each input = 4.02k/1k divider (/5.02, +/-5 V -> +/-1.0 V) + 10 nF (~20 kHz). CH0 = V DC monitor, CH1 = I_HI, CH2 = I_LO, CH3 = AC V monitor. Clock: Pico GP21 8.000 MHz (R47 -> J16 pin 7) or the HAT oscillator (needed wi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
POWER: external +/-15 V bench supply (Schottky reverse protection, ferrite filtering). L7805 -> +5 V (relays, DAC, Pico VSYS). MCP1700 -> +3V3, split by ferrites into +3V3A (ADC analog) and +3V3D (ADC digital, oscillator, logic pull-ups).
CONTROL: Pico 2 or Waveshare ESP32-S3-ETH (socketed; same header pins) -> SPI -> U27/U28 74HC595 -> CTL0..15 -> 2x TBD62783A high-side drivers -> relay coils. U27 QA..QH = CTL0..7, U28 QA..QH = CTL8..15 (MOSI -> U27 -> U28). Driver channel m (KDm) is driven by CTL(15-m); the order is for routing, f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
BIAS DAC (on the HAT, via J17): DAC80501M (midscale at power-up) 0..5 V -> U11: V_DAC_BIAS = 10.05 V - 4.02*V_DAC (+10..-10 V, 0 V at midscale). Connected to the summer only when K21 closes (firmware sets range first).
Op-amp decoupling: one pair per op-amp, place at each op-amp supply pin.
DRIVE INPUTS: BIAS/PULSE (DC) + AC PROBE (AC-coupled, JP3 = x1 or x0.1) + on-board bias DAC (via K21), summed by U9 and re-inverted by U10: VSET = V_bias + V_dac + k*V_ac.
HIGH-GAIN TIA U5: WE = SUM_HI virtual ground. Ranges K1..K6 = 1k, 10k, 100k, 1M, 10M, 100M (relays on the output side). 1 MHz C-V: use 1k and 10k only (100k and up roll off below 1 MHz). Q1/Q2 C-B junctions: low-leakage steering to the low-gain TIA U6.
CONTROL AMP U1: K7 DEV = follower (CE = VSET). K8 PSTAT (K7 off) = PI loop, V_RE = VSET. K9 RE_LOCAL ties RE sense to CE_INT. K10 CELL connects CE_INT to the CE BNC (open = cell disconnected). Cal loads (K11/K13) are T-switched: off -> mid node grounded by K12/K14 (NC).
RE: U2 electrometer follower, U3 guard driver (RE BNC shell + GUARD BNC), U7 RE_MON buffer (keeps monitor and nuller load off U2). V_OUT BNC: K19 (NC) = DC monitor V_RE/2 (U4); VMODE on -> K20 = AC monitor x10.1, AC-coupled ~100 Hz (U8).
NULLER (vector): U12 makes -V_RE. RV1 (0..-1) -> U13 -> 100p (+910p via K17) injects -jwC.V (C null). RV2 (+1..-1) -> U14 -> 220n -> 20k (2k via K18) injects G null, AC-coupled (no DC into WE). K15/K16 (NULL_EN) connect to SUM_HI.
U10
U11
U12
U13
U14
Pico ground joins GND only via FB5 (JP5 hard-tie)
Mounting holes: H1 = the only chassis bond (GND, by J1 star point); H2-H9 isolated M3; H10-H13 M2.5 HAT standoffs
FRONT PANEL (off-board): 10-turn 10k pots + counting dials
(Bourns 3590S-2-103). Shielded 3-core cable to J14/J15,
shield to pin 4 (GND) at the board end only.
Driver decoupling
J16: ADC/DAC sub-board (adc_hat/, Pi Zero pHAT outline). SPI0 = 19/21/23, CE0 24 = CS_ADC, CE1 26 = CS_DAC, GPIO4 (7, GPCLK0) = HAT_CLK from Pico GP21 via R47, GPIO24 (18) = ADC_SYNC, GPIO25 (22) = ADC_DRDY. J17: analog link to the sub-board, 1x12: ADC0P,GND, ADC1P,GND, ADC2P,GND, ADC3P,GND, NC (HA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
